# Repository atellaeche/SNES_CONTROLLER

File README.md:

# Uzebox & SNES Modular Joystick PCB

This dual layer, 57mm x 76mm modular joystick PCB was created using [KiCAD](https://www.kicad.org/) by [Uzebox forum](https://uzebox.org/forums/index.php) member altella with help from [taylor-madeak](https://github.com/taylor-madeak) and [danboid](https://github.com/danboid).

See the [Uzebox Joystick wiki page](https://uzebox.org/wiki/Joystick) for more info on how to use this PCB.

## Project Goals

1. Provide a beginner-friendly circuit board design by using all off-the-shelf through-hole components and screw terminals for the button interfaces.
1. Maintain compatibility with both the Uzebox console and its variants as well as all variants (including PAL region consoles) of the original Nintendo Super Famicom/Super NES console.

## Legal Disclaimers

1. This project is in no way affiliated with, licensed by, or endorsed by **Nintendo Co., Ltd.** or their respected partners and subsidiaries.  The names **Nitendo," "Super Nintendo Entertainment System," and "Super Famicom"** are all registered trademarks of Nintendo Co., Ltd. and are used here for context reference only.
1. This project is offered without warranty of any kind, and the authors **ASSUME NO LIABILITY** for material, physical, or immaterial damages caused by the use or non-use of this design.

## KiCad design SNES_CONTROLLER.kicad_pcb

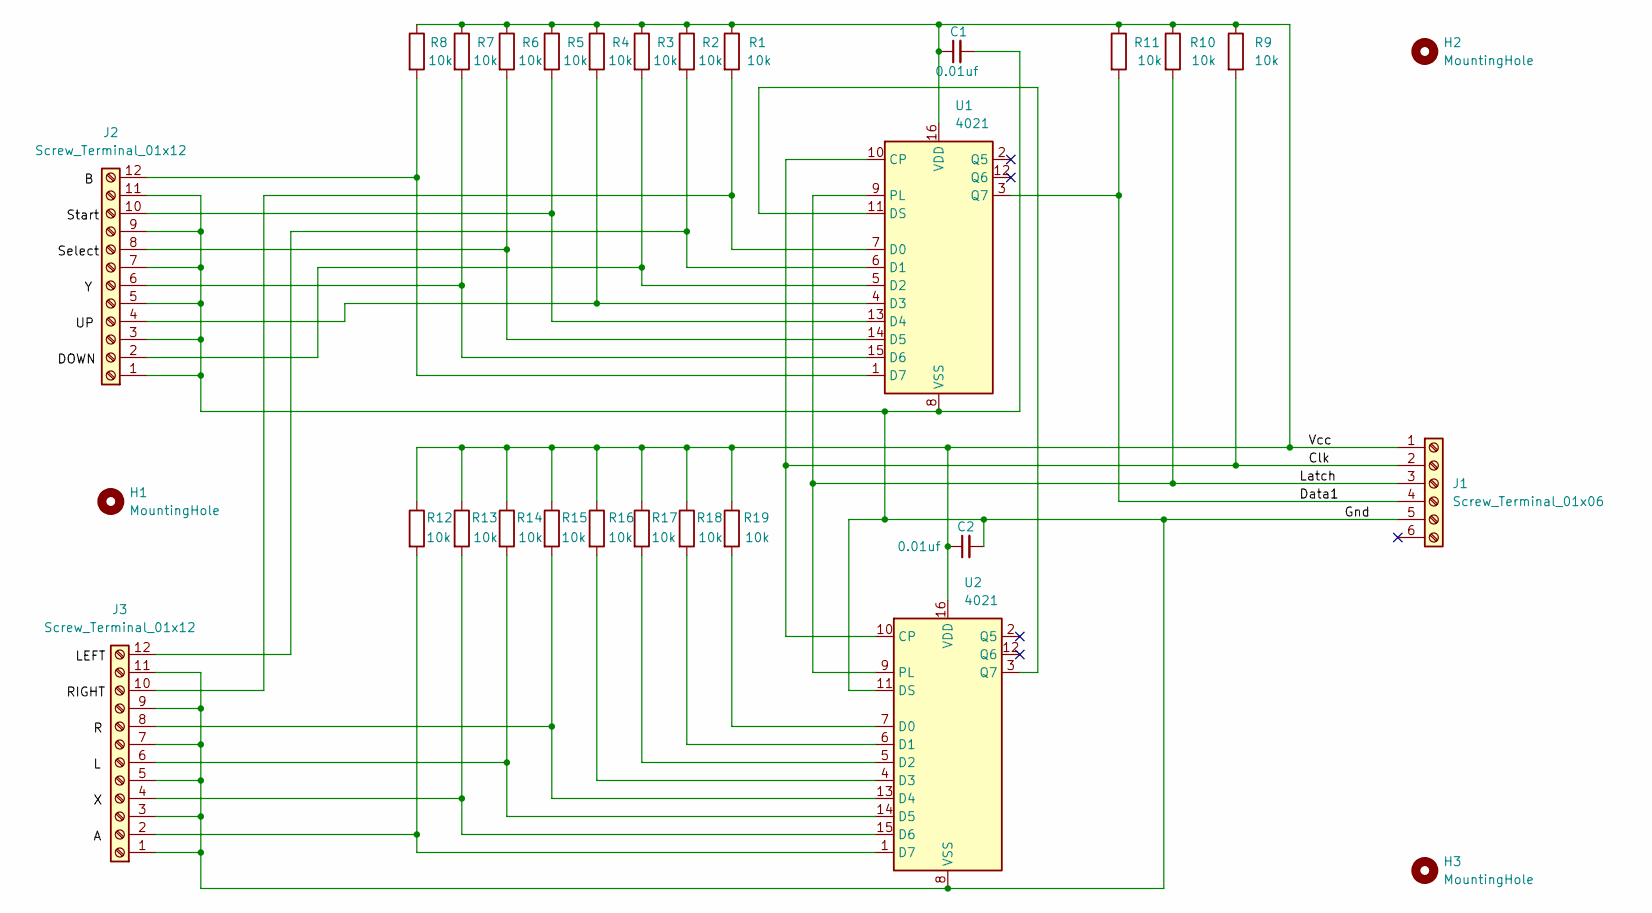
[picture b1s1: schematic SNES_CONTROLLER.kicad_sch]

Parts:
C1, C2: 0.01uf; C_Disc_D3.0mm_W1.6mm_P2.50mm
H1, H2, H3: MountingHole; MountingHole_4.3mm_M4
J1: Screw_Terminal_01x06; TerminalBlock_MaiXu_MX126-5.0-06P_1x06_P5.00mm
J2, J3: Screw_Terminal_01x12; TerminalBlock_MaiXu_MX126-5.0-12P_1x12_P5.00mm
R1, R2, R3, R4, R5, R6, R7, R8, R9, R10, R11, R12, R13, R14, R15, R16, R17, R18, R19: 10k; R_Axial_DIN0207_L6.3mm_D2.5mm_P5.08mm_Vertical
U1, U2: 4021; DIP-16_W7.62mm

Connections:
/Clk: J1.2, R9.2, U1.10 (CP), U2.10 (CP)
/Data1: J1.4, R11.2, U1.3 (Q7)
/Gnd: C1.2, C2.2, J1.5, J1.6, J2.1, J2.3, J2.5, J2.7, J2.9, J2.11, J3.1, J3.3, J3.5, J3.7, J3.9, J3.11, U1.8 (VSS), U2.8 (VSS), U2.11 (DS)
/Latch: J1.3, R10.2, U1.9 (PL), U2.9 (PL)
/Vcc: C1.1, C2.1, J1.1, R1.1, R2.1, R3.1, R4.1, R5.1, R6.1, R7.1, R8.1, R9.1, R10.1, R11.1, R12.1, R13.1, R14.1, R15.1, R16.1, R17.1, R18.1, R19.1, U1.16 (VDD), U2.16 (VDD)
unnamed: J2.2, R3.2, U1.5 (D2)
unnamed: J2.4, R4.2, U1.4 (D3)
unnamed: J2.6, R7.2, U1.15 (D6)
unnamed: J2.8, R6.2, U1.14 (D5)
unnamed: J2.10, R5.2, U1.13 (D4)
unnamed: J2.12, R8.2, U1.1 (D7)
unnamed: J3.2, R12.2, U2.1 (D7)
unnamed: J3.4, R13.2, U2.15 (D6)
unnamed: J3.6, R14.2, U2.14 (D5)
unnamed: J3.8, R15.2, U2.13 (D4)
unnamed: J3.10, R1.2, U1.7 (D0)
unnamed: J3.12, R2.2, U1.6 (D1)
unnamed: U1.11 (DS), U2.3 (Q7)
unnamed: R19.2, U2.7 (D0)
unnamed: R18.2, U2.6 (D1)
unnamed: R17.2, U2.5 (D2)
unnamed: R16.2, U2.4 (D3)

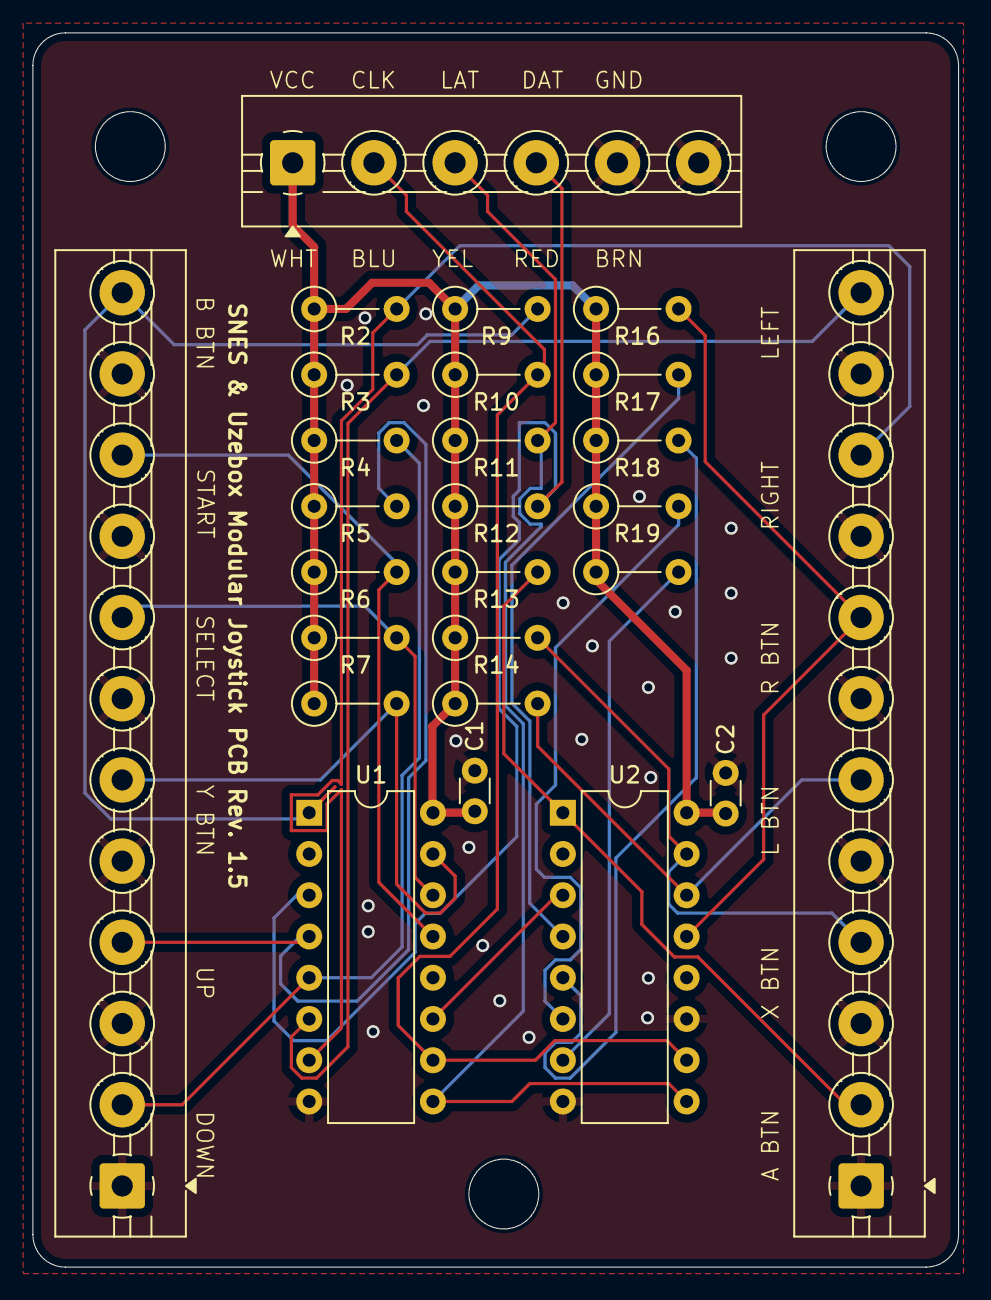
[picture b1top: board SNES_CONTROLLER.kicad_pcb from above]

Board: 2 copper layers, 57.0 x 76.0 mm, 29 parts (0 on the bottom side), 22 nets.

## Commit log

2025-02-06 development
2025-02-07 SNES HW controller Version 1.0
2025-02-09 SNES CONTROLLER v2
2025-02-26 Error corrected. Pin 11 of second 4021 connected to GND
2025-03-04 added schematics PDF and ZIP file with Gerbers and drill files
2025-03-05 Deleted old PNG files
2025-03-06 Add silkscreen
2025-03-06 Update gerber files
2025-03-20 Add labels to front silkscreen and mount holes
2025-04-01 v1.2 - Use M4 mount holes
2025-04-02 Move mount holes and top silkscreen labels - v1.3
2025-04-17 changes reverted. Connector changed by a 6 pin one. Rounded PCB
2025-04-17 Add silkscreens and M4 mount holes
2025-04-17 Add PCB spec to README
2025-04-24 Add link in README to Uzebox Joystick wiki page
2025-04-24 Add PCB pic
2025-04-24 Change PCB pic URL for altellas repo
2025-05-03 Update README to note that it doesn't work with the SNES yet
2025-05-06 Add decoupling capacitors for ICs
2025-05-06 Move old docs into doc directory
2025-05-06 Move gerbers into their own directory
2025-05-06 Move docs into their own directory
2025-05-06 Refactor schematic and board
2025-05-06 Update project files
2025-05-06 Add new doc images and renders
2025-05-06 Update repo README file
2025-05-07 Add custom Power netclass for power rails
2025-05-07 Remove mistakenly committed backups directory
2025-05-07 Replace v1.5 3D render with better quality
2025-05-07 Fix typo in README
2025-05-07 Add BOM information to project
2025-05-09 Add IC sockets to project
2025-05-09 Update docs
2025-05-13 Fix Digikey BOM preset
2025-05-13 Add gerbers and BOM files for v1.5
